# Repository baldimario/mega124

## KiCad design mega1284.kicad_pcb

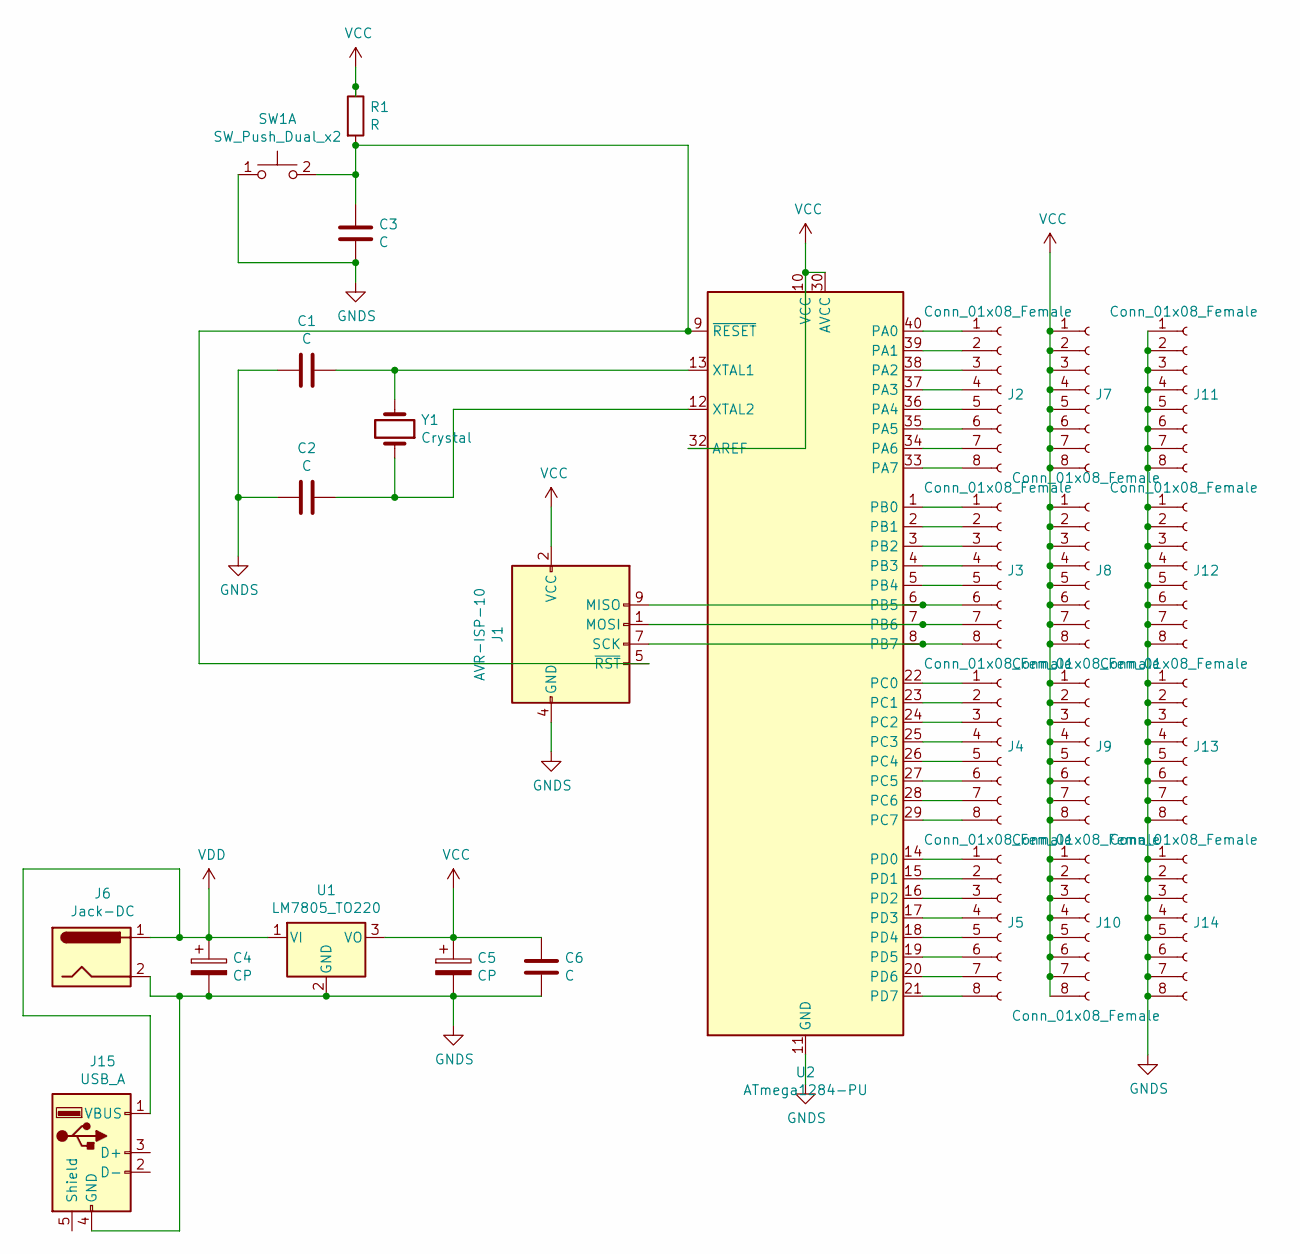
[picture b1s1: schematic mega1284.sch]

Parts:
C1, C2, C3: C; CP_Radial_Tantal_D4.5mm_P2.50mm
C4, C5: CP; CP_Radial_D5.0mm_P2.50mm
C6: C; CP_Radial_Tantal_D5.0mm_P2.50mm
J1: AVR-ISP-10; PinHeader_2x05_P2.54mm_Vertical
J2, J3, J4, J5, J7, J8, J9, J10, J11, J12, J13, J14: Conn_01x08_Female; PinHeader_1x08_P2.54mm_Vertical
J6: Jack-DC; BarrelJack_CUI_PJ-102AH_Horizontal
J15: USB_A; USB_A_Molex_67643_Horizontal
R1: R; R_Axial_DIN0309_L9.0mm_D3.2mm_P12.70mm_Horizontal
SW1: SW_Push_Dual_x2; SW_TH_Tactile_Omron_B3F-10xx
U1: LM7805_TO220; TO-220-3_Vertical
U2: ATmega1284-PU; DIP-40_W15.24mm
Y1: Crystal; Crystal_HC49-U_Vertical

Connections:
GNDS: C1.2, C2.2, C3.2, C4.2, C5.2, C6.2, J1.4 (GND), J1.6 (GND), J1.8 (GND), J1.10 (GND), J6.2, J11.1, J11.2, J11.3, J11.4, J11.5, J11.6, J11.7, J11.8, J12.1, J12.2, J12.3, J12.4, J12.5, J12.6, J12.7, J12.8, J13.1, J13.2, J13.3, J13.4, J13.5, J13.6, J13.7, J13.8, J14.1, J14.2, J14.3, J14.4, J14.5, J14.6, J14.7, J14.8, J15.4 (GND), SW1.1 (C), U1.2 (GND), U2.11 (GND), U2.31 (GND)
unnamed: C1.1, U2.13 (XTAL1), Y1.2
unnamed: C2.1, U2.12 (XTAL2), Y1.1
unnamed: C3.1, J1.5 (~RST), R1.2, SW1.2 (D), U2.9 (~RESET)
unnamed: J1.1 (MOSI), J3.7, U2.7 (PB6)
unnamed: J1.7 (SCK), J3.8, U2.8 (PB7)
unnamed: J1.9 (MISO), J3.6, U2.6 (PB5)
unnamed: J2.1, U2.40 (PA0)
unnamed: J2.2, U2.39 (PA1)
unnamed: J2.3, U2.38 (PA2)
unnamed: J2.4, U2.37 (PA3)
unnamed: J2.5, U2.36 (PA4)
unnamed: J2.6, U2.35 (PA5)
unnamed: J2.7, U2.34 (PA6)
unnamed: J2.8, U2.33 (PA7)
unnamed: J3.1, U2.1 (PB0)
unnamed: J3.2, U2.2 (PB1)
unnamed: J3.3, U2.3 (PB2)
unnamed: J3.4, U2.4 (PB3)
unnamed: J3.5, U2.5 (PB4)
unnamed: J4.1, U2.22 (PC0)
unnamed: J4.2, U2.23 (PC1)
unnamed: J4.3, U2.24 (PC2)
unnamed: J4.4, U2.25 (PC3)
unnamed: J4.5, U2.26 (PC4)
unnamed: J4.6, U2.27 (PC5)
unnamed: J4.7, U2.28 (PC6)
unnamed: J4.8, U2.29 (PC7)
unnamed: J5.1, U2.14 (PD0)
unnamed: J5.2, U2.15 (PD1)
unnamed: J5.3, U2.16 (PD2)
unnamed: J5.4, U2.17 (PD3)
unnamed: J5.5, U2.18 (PD4)
unnamed: J5.6, U2.19 (PD5)
unnamed: J5.7, U2.20 (PD6)
unnamed: J5.8, U2.21 (PD7)
VCC: C5.1, C6.1, J1.2 (VCC), J7.1, J7.2, J7.3, J7.4, J7.5, J7.6, J7.7, J7.8, J8.1, J8.2, J8.3, J8.4, J8.5, J8.6, J8.7, J8.8, J9.1, J9.2, J9.3, J9.4, J9.5, J9.6, J9.7, J9.8, J10.1, J10.2, J10.3, J10.4, J10.5, J10.6, J10.7, J10.8, R1.1, U1.3 (VO), U2.10 (VCC), U2.30 (AVCC), U2.32 (AREF)
VDD: C4.1, J6.1, J15.1 (VBUS), U1.1 (VI)

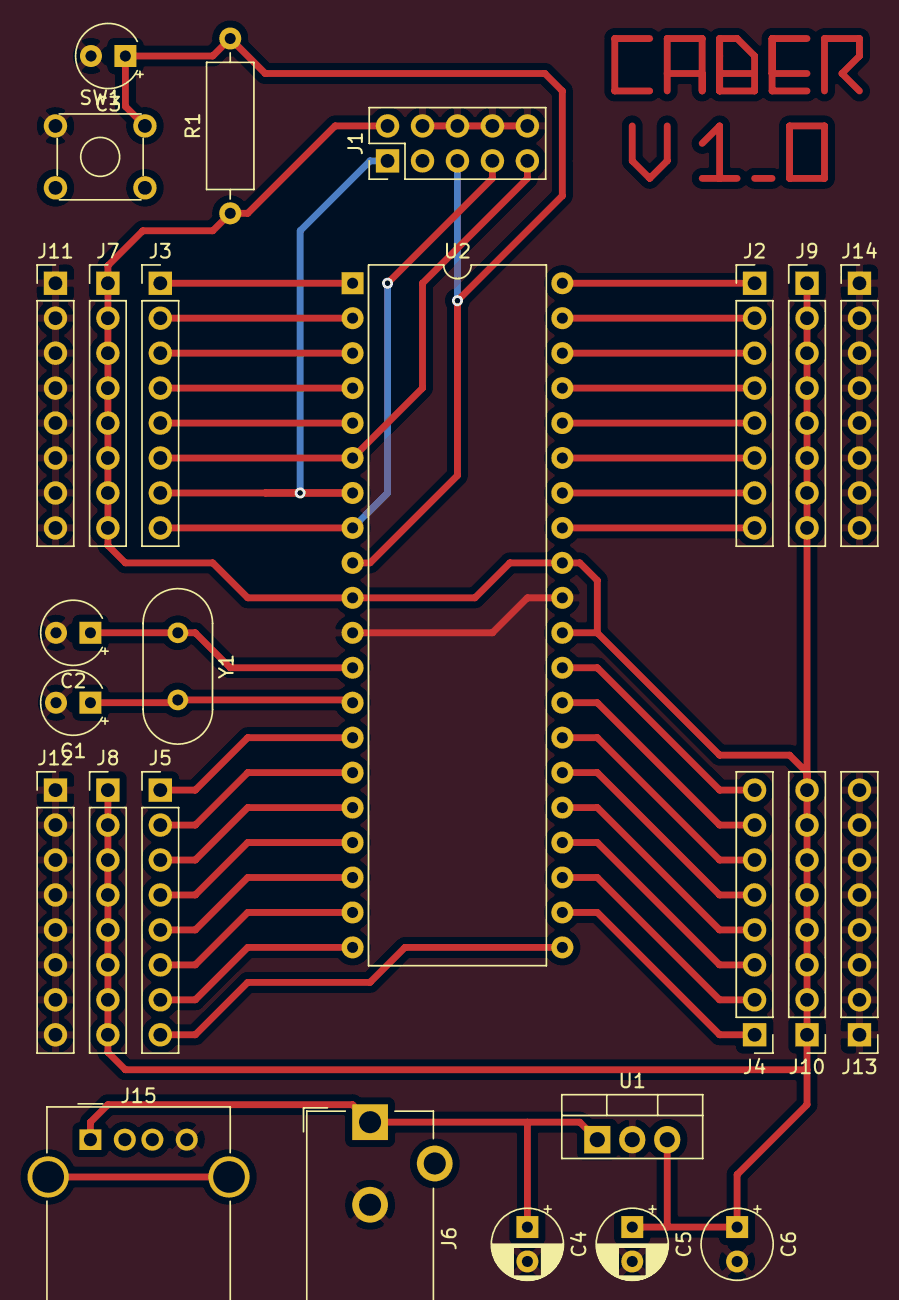
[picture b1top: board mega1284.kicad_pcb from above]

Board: 2 copper layers, 26 parts (0 on the bottom side), 38 nets.
